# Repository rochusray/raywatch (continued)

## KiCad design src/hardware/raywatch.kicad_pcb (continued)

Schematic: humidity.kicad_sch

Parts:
C48: 100nF; C_0402_1005Metric
J57, J58: Conn_01x02_Pin; PinHeader_1x02_P1.27mm_Vertical
U18: ENS210-LQFM; XDCR_ENS210-LQFM; PARTREV 5

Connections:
+1V8: C48.1, J58.1, U18.1 (VDD); also elsewhere on the board
/Humidity/SCL1V8: J57.1, U18.2 (SCL)
/Humidity/SDA1V8: J57.2, U18.3 (SDA)
GND: C48.2, J58.2, U18.4 (VSS), U18.5 (VSS); also elsewhere on the board

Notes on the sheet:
I²C: 1000011

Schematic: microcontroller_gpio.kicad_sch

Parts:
J17, J21: Conn_02x08_Odd_Even; PinHeader_2x08_P1.27mm_Vertical
J18, J19, J20: Conn_01x02_Pin; PinHeader_1x02_P1.27mm_Vertical
R12, R13: 10kΩ; R_0402_1005Metric
U3, U4: PCAL6416AHF_128; QFN50P400X400X80-25N; PARTREV 7.1

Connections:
/GPIO/EXP1INT: J20.1, U4.22 (~INT)
/GPIO/EXP2INT: J20.2, U3.22 (~INT)
/GPIO/SCL: J19.1, U3.19 (SCL), U4.19 (SCL)
/GPIO/SDA: J19.2, U3.20 (SDA), U4.20 (SDA)
GND: J18.2, U3.9 (VSS), U3.25 (EXP), U4.9 (VSS), U4.18 (ADDR), U4.25 (EXP); also elsewhere on the board
unnamed: J17.1, U3.8 (P0_7)
unnamed: J17.2, U3.10 (P1_0)
unnamed: J17.3, U3.7 (P0_6)
unnamed: J17.4, U3.11 (P1_1)
unnamed: J17.5, U3.6 (P0_5)
unnamed: J17.6, U3.12 (P1_2)
unnamed: J17.7, U3.5 (P0_4)
unnamed: J17.8, U3.13 (P1_3)
unnamed: J17.9, U3.4 (P0_3)
unnamed: J17.10, U3.14 (P1_4)
unnamed: J17.11, U3.3 (P0_2)
unnamed: J17.12, U3.15 (P1_5)
unnamed: J17.13, U3.2 (P0_1)
unnamed: J17.14, U3.16 (P1_6)
unnamed: J17.15, U3.1 (P0_0)
unnamed: J17.16, U3.17 (P1_7)
unnamed: J21.1, U4.8 (P0_7)
unnamed: J21.2, U4.10 (P1_0)
unnamed: J21.3, U4.7 (P0_6)
unnamed: J21.4, U4.11 (P1_1)
unnamed: J21.5, U4.6 (P0_5)
unnamed: J21.6, U4.12 (P1_2)
unnamed: J21.7, U4.5 (P0_4)
unnamed: J21.8, U4.13 (P1_3)
unnamed: J21.9, U4.4 (P0_3)
unnamed: J21.10, U4.14 (P1_4)
unnamed: J21.11, U4.3 (P0_2)
unnamed: J21.12, U4.15 (P1_5)
unnamed: J21.13, U4.2 (P0_1)
unnamed: J21.14, U4.16 (P1_6)
unnamed: J21.15, U4.1 (P0_0)
unnamed: J21.16, U4.17 (P1_7)
unnamed: R12.2, U3.24 (~RESET)
unnamed: R13.2, U4.24 (~RESET)

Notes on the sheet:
I²C: 0100000

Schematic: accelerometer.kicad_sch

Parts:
C26, C27, C33, C34: 10µF; C_0402_1005Metric
C28, C29, C30, C31, C32, C35, C36, C37, C38: 100nF; C_0402_1005Metric
J37, J38, J39, J40, J41, J42, J43, J44, J45: Conn_01x02_Pin; PinHeader_1x02_P1.27mm_Vertical
U10, U11, U13, U14: LIS2DUX12TR; LGA-12_2.0X2.0X0.74_LIS2DUX12_STM
U12: TPS22916BYFPR; IC_TPS22916BYFPR; PARTREV F
Y3: DSC6003CE2A; OSC_DSC6003CE2A-000.0000; PARTREV B

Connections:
+1V8: C26.2, C27.2, C29.2, C31.2, C33.2, C34.2, C35.2, C37.2, J38.1, U10.9 (VDD), U11.9 (VDD), U13.9 (VDD), U14.9 (VDD); also elsewhere on the board
/Accelerometer/ACC1INT1: J41.1, U10.12 (INT1)
/Accelerometer/ACC1INT2: J41.2, U10.11 (INT2)
/Accelerometer/ACC2INT1: J43.1, U13.12 (INT1)
/Accelerometer/ACC2INT2: J43.2, U13.11 (INT2)
/Accelerometer/ACC3INT1: J42.1, U11.12 (INT1)
/Accelerometer/ACC3INT2: J42.2, U11.11 (INT2)
/Accelerometer/ACC4INT1: J44.1, U14.12 (INT1)
/Accelerometer/ACC4INT2: J44.2, U14.11 (INT2)
/Accelerometer/ACCCLK: U10.7 (RES), U11.7 (RES), U13.7 (RES), U14.7 (RES), Y3.3 (OUT)
/Accelerometer/ACCCLKEN: J45.1, U12.B2 (ON)
/Accelerometer/ACCCLKFS: J45.2, Y3.1 (OE)
/Accelerometer/SCL: J39.1, U11.1 (SCL/SPC), U14.1 (SCL/SPC)
/Accelerometer/SCL2: J40.1, U10.1 (SCL/SPC), U13.1 (SCL/SPC)
/Accelerometer/SDA: J39.2, U11.4 (SDA/SDI/SDO), U14.4 (SDA/SDI/SDO)
/Accelerometer/SDA2: J40.2, U10.4 (SDA/SDI/SDO), U13.4 (SDA/SDI/SDO)
GND: C26.1, C27.1, C28.2, C29.1, C30.2, C31.1, C32.2, C33.1, C34.1, C35.1, C36.2, C37.1, C38.2, J37.2, J38.2, U10.5 (NC), U10.6 (GND), U10.8 (GND), U11.5 (NC), U11.6 (GND), U11.8 (GND), U12.B1 (GND), U13.3 (SDO/SA0), U13.5 (NC), U13.6 (GND), U13.8 (GND), U14.3 (SDO/SA0), U14.5 (NC), U14.6 (GND), U14.8 (GND), Y3.2 (GND); also elsewhere on the board
unnamed: C28.1, U12.A1 (VOUT), Y3.4 (VDD)

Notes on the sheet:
I²C: 0011001
I²C: 0011000
Optional

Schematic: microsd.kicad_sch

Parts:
C39: 10µF; C_0402_1005Metric
C40: 100nF; C_0402_1005Metric
J46, J47: Conn_01x02_Pin; PinHeader_1x02_P1.27mm_Vertical
J48: Conn_01x04_Pin; PinHeader_1x04_P1.27mm_Vertical
J49: MSD-1-A; CUI_MSD-1-A; PARTREV 1.0
R19, R20, R25: 28Ω; R_0402_1005Metric
R21, R22, R23, R24, R26: 10kΩ; R_0402_1005Metric
U15: TPS22916BYFPR; IC_TPS22916BYFPR; PARTREV F

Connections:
/microSD/CS: J48.4, R25.1
/microSD/MISO: J48.3, J49.7 (DAT0), R21.2
/microSD/MOSI: J48.2, R20.1
/microSD/MSD3V3: C39.1, C40.1, J49.4 (VDD), R21.1, R22.1, R23.1, R24.1, U15.A1 (VOUT)
/microSD/MSDDET: J46.2, R26.1
/microSD/MSDEN: J46.1, U15.B2 (ON)
/microSD/SCK: J48.1, R19.1
GND: C39.2, C40.2, J47.2, J49.6 (VSS), J49.G1 (COVER_GND), J49.G2 (COVER_GND), J49.G3 (COVER_GND), J49.G4 (COVER_GND), U15.B1 (GND); also elsewhere on the board
unnamed: J49.2 (CD/DAT3), R24.2, R25.2
unnamed: J49.5 (CLK), R19.2
unnamed: J49.3 (CMD), R20.2
unnamed: J49.8 (DAT1), R22.2
unnamed: J49.1 (DAT2), R23.2
unnamed: J49.CD, R26.2

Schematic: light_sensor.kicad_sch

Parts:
C60: 1µF; C_0402_1005Metric; Tolerance 20%
J65, J66: Conn_01x02_Pin; PinHeader_1x02_P1.27mm_Vertical
U24: LTR-329ALS-01; IC_LTR-329ALS-01; PARTREV 1.8

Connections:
/Light Sensor/SCL: J66.1, U24.4 (SCL)
/Light Sensor/SDA: J66.2, U24.3 (SDA)
GND: C60.2, J65.2, U24.2 (GND); also elsewhere on the board

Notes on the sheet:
I²C: 0101001

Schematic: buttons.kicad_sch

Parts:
C18, C19, C20, C21: 10nF; C_0402_1005Metric
J22: Conn_01x02_Pin; PinHeader_1x02_P1.27mm_Vertical
J23: Conn_01x04_Pin; PinHeader_1x04_P1.27mm_Vertical
R14, R15, R16, R17: 200kΩ; R_0402_1005Metric
S1, S2, S3, S4: EVQ-P7A01P; SW_EVQ-P7A01P; PARTREV 2022.4

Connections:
/Buttons/BTN1: C18.1, J23.1, R14.2
/Buttons/BTN2: C19.1, J23.2, R15.2
/Buttons/BTN3: C20.1, J23.3, R16.2
/Buttons/BTN4: C21.1, J23.4, R17.2
GND: J22.2, S1.1_1, S1.1_2, S2.1_1, S2.1_2, S3.1_1, S3.1_2, S4.1_1, S4.1_2; also elsewhere on the board
unnamed: R14.1, S1.2_1, S1.2_2
unnamed: R15.1, S2.2_1, S2.2_2
unnamed: R16.1, S3.2_1, S3.2_2
unnamed: R17.1, S4.2_1, S4.2_2

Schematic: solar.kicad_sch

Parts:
B1, B2: KXOB25-05X3F-TR; CHIP2_KXOB25-05X3F-TR_AAR
C77, C78, C79: 10µF; C_0402_1005Metric
J86: Conn_01x02_Pin; PinHeader_1x02_P1.27mm_Vertical
L9: 2.2µH; L_0402_1005Metric
R39: 400KΩ; R_0402_1005Metric
R40: 100KΩ; R_0402_1005Metric
U33: TPS61099YFFT; YFF0006AFAD

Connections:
GND: B1.1, B2.1, C77.2, C78.2, C79.2, J86.2, R40.2, U33.A2 (GND); also elsewhere on the board
unnamed: B1.2, B2.2, C77.1, L9.1, U33.A1 (VIN), U33.C1 (EN)
unnamed: R39.2, R40.1, U33.C2 (FB)
unnamed: L9.2, U33.B1 (SW)
VSOLAR: C78.1, C79.1, J86.1, R39.1, U33.B2 (VOUT); also elsewhere on the board

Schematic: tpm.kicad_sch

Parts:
C25: 100nF; C_0402_1005Metric
J35, J36: Conn_01x02_Pin; PinHeader_1x02_P1.27mm_Vertical
U9: ATECC608A-MAHDA-S; SON50P200X300X60-9N

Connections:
/TPM/SCL: J36.1, U9.6 (SCL)
/TPM/SDA: J36.2, U9.5 (SDA)
GND: C25.2, J35.2, U9.4 (GND), U9.9 (GND_PAD); also elsewhere on the board

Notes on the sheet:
Default I²C: 1100000

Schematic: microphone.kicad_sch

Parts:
C96: 100nF; C_0402_1005Metric
J90, J91: Conn_01x02_Pin; PinHeader_1x02_P1.27mm_Vertical
U36: IM72D128V01XTMA1; PG-LLGA-5-3_INF

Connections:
/Microphone/PDMCLK: J91.2, U36.3 (CLOCK)
/Microphone/PDMDATA: J91.1, U36.1 (DATA)
GND: C96.2, J90.2, U36.4 (SELECT), U36.5 (GND); also elsewhere on the board

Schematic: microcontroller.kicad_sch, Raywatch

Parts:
ANT1: SR4W035; SR4W035_4X6_ANT
ANT2: W3102; IND_W3102; PARTREV 1944
C1: 1.5pF; C_0402_1005Metric; Rated Voltage 25V; Tolerance 0.05pF
C2: 2pF; C_0402_1005Metric; Rated Voltage 25V; Tolerance 0.05pF
C3: 3.9pF; C_0402_1005Metric
C4: 3pF; C_0402_1005Metric; Rated Voltage 50V; Tolerance 0.1pF
C5: 1.5pF; C_0402_1005Metric; Rated Voltage 50V; Tolerance 20%
C6, C11, C13, C15: 100nF; C_0402_1005Metric; Rated Voltage 3.3V; Tolerance 10%
C7, C8: 27pF; C_0402_1005Metric; Tolerance 2%
C9: 10µF; C_0402_1005Metric; Rated Voltage 6.3V; Tolerance 20%
C10, C17: 2.2µF; C_0402_1005Metric; Rated Voltage 3.3V; Tolerance 20%
C12: 2.2nF; C_0402_1005Metric; Rated Voltage 10V; Tolerance 10%
C14: 10nF; C_0402_1005Metric; Rated Voltage 6.3V
C16: 100pF; C_0402_1005Metric
FB1: 120Ω; L_0402_1005Metric
J1: Conn_02x05_Odd_Even; PinHeader_2x05_P1.27mm_Vertical
J2, J3, J4, J5, J12, J13: Conn_01x02_Pin; PinHeader_1x02_P1.27mm_Vertical
J6, J7, J8, J9, J10, J11: Conn_01x04_Pin; PinHeader_1x04_P1.27mm_Vertical
J14, J15, J16: Conn_02x08_Odd_Even; PinHeader_2x08_P1.27mm_Vertical
L1: 2.7nH; L_0402_1005Metric
L2, L3: 2.5nH; L_0402_1005Metric
L4: -; L_0402_1005Metric; not fitted
L5: 2.2nH; L_0402_1005Metric
L6: 4.7µH; L_0402_1005Metric; Tolerance 20%
R1, R2, R3: 1kΩ; R_0402_1005Metric
R4: 200kΩ; R_0402_1005Metric
R5: 100kΩ; R_0402_1005Metric
R6, R7, R8, R9, R10, R11: 10kΩ; R_0402_1005Metric
U1: NRF54L15-QFAA-R; QFN40P600X600X90-49N; PARTREV 0.8
U2: PCA9306DQER; SON35P140X100X40-8N
Y1: ABS07-32.768KHZ-7-T; XTAL_ABS07-32.768KHZ-7-T; PARTREV 08.19.15
Y2: ECS-320-8-37B-CKY-TR; XTAL_ECS-160-9-37-CKM-TR; PARTREV 2017

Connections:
+1V8: J3.1, U2.2 (VREF1); also elsewhere on the board
/MC: Microcontroller/ANT: J13.1, L1.2, U1.31 (ANT)
/MC: Microcontroller/NFC1: ANT2.1, C7.2, J2.1, U1.3 (P1.02/NFC1)
/MC: Microcontroller/NFC2: ANT2.2, C8.1, J2.2, U1.4 (P1.03/NFC2)
/MC: Microcontroller/P2.07: J1.6, J10.2, U1.18 (P2.07/TRACEDATA(0)/SWO)
/MC: Microcontroller/PDMCLK: J12.2, U1.42 (P1.14/RADIO(5)/AIN7)
/MC: Microcontroller/PDMDATA: J12.1, R5.1, U1.41 (P1.13/RADIO(4)/AIN6)
/MC: Microcontroller/SCL: J15.2, J15.4, J15.6, J15.8, J15.10, J15.12, J15.14, J15.16, R7.1, U1.28 (P0.03/GRTCPWM), U2.6 (SCL2)
/MC: Microcontroller/SCL1V8: J16.2, J16.4, J16.6, J16.8, J16.10, J16.12, J16.14, J16.16, R9.1, U2.3 (SCL1)
/MC: Microcontroller/SCL2: J14.2, J14.4, J14.6, J14.8, J14.10, J14.12, J14.14, J14.16, R11.1, U1.9 (P1.08/CLK16M/EXTREF)
/MC: Microcontroller/SDA: J15.1, J15.3, J15.5, J15.7, J15.9, J15.11, J15.13, J15.15, R6.1, U1.27 (P0.02), U2.5 (SDA2)
/MC: Microcontroller/SDA1V8: J16.1, J16.3, J16.5, J16.7, J16.9, J16.11, J16.13, J16.15, R8.1, U2.4 (SDA1)
/MC: Microcontroller/SDA2: J14.1, J14.3, J14.5, J14.7, J14.9, J14.11, J14.13, J14.15, R10.1, U1.8 (P1.07/ASI(1)/AIN3)
/MC: Microcontroller/VSSPA: C1.2, J13.2, U1.32 (VSS_PA)
/MC: Microcontroller/XC1: U1.34 (XC1), Y2.1 (IN/OUT)
/MC: Microcontroller/XC2: U1.35 (XC2), Y2.3 (OUT/IN)
GND: ANT1.3 (GND), ANT1.4 (GND), ANT1.6 (GND), C2.2, C3.1, C4.2, C6.2, C7.1, C8.2, C9.2, C10.2, C11.1, C12.2, C13.1, C14.2, C15.2, C16.2, C17.2, J1.3, J1.5, J1.9, J3.2, J4.2, J6.4, J7.4, J11.4, L4.2, L5.2, R5.2, R6.2, R7.2, R8.2, R9.2, R10.2, R11.2, U1.44 (VSS), U1.49 (VSS), U2.1 (GND), Y2.2 (GND), Y2.4 (GND); also elsewhere on the board
unnamed: ANT1.2 (FEED), C5.2, L5.1
unnamed: C1.1, L1.1, L2.2
unnamed: C2.1, L2.1, L3.2
unnamed: C4.1, C5.1, L3.1, L4.1
unnamed: J1.2, U1.25 (SWDIO)
unnamed: J1.4, U1.26 (SWDCLK)
unnamed: J1.10, R1.1
unnamed: J5.1, R2.1
unnamed: J5.2, R3.1
unnamed: J6.1, U1.5 (P1.04/ASO(0)/AIN0)
unnamed: J6.2, U1.6 (P1.05/ASI(0)/RADIO(6)/AIN1)
unnamed: J6.3, U1.7 (P1.06/ASO(1)/AIN2)
unnamed: J7.1, U1.23 (P0.00)
unnamed: J7.2, U1.24 (P0.01)
unnamed: J7.3, U1.29 (P0.04/GRTCLFCLKOUT)
unnamed: J8.1, U1.37 (P1.09/ASO(2)/RADIO(0))
unnamed: J8.2, U1.38 (P1.10/ASI(2)/RADIO(1))
unnamed: J8.3, U1.39 (P1.11/ASO(3)/RADIO(2)/AIN4)
unnamed: J8.4, U1.40 (P1.12/ASI(3)/RADIO(3)/AIN5)
unnamed: J9.1, U1.11 (P2.00)
unnamed: J9.2, U1.12 (P2.01)
unnamed: J9.3, U1.13 (P2.02)
unnamed: J9.4, U1.14 (P2.03)
unnamed: J10.1, U1.17 (P2.06/TRACECLK)
unnamed: J10.3, U1.19 (P2.08/TRACEDATA(1))
unnamed: J10.4, U1.20 (P2.09/TRACEDATA(2))
unnamed: J11.1, U1.15 (P2.04)
unnamed: J11.2, U1.16 (P2.05)
unnamed: J11.3, U1.21 (P2.10/TRACEDATA(3))
unnamed: L6.2, U1.46 (DCC)
unnamed: C12.1, C14.1, C17.1, FB1.1, U1.33 (DECRF), U1.43 (DECA)
unnamed: C10.1, FB1.2, L6.1, U1.45 (DECD)
unnamed: U1.1 (P1.00/XL1), Y1.2
unnamed: U1.2 (P1.01/XL2), Y1.1
unnamed: C3.2, R1.2, R2.2, R3.2, U1.30 (~RESET)
unnamed: C16.1, R4.1, U2.7 (VREF2), U2.8 (EN)

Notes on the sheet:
Matching using reference board circuit
Matching just eyeballed

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
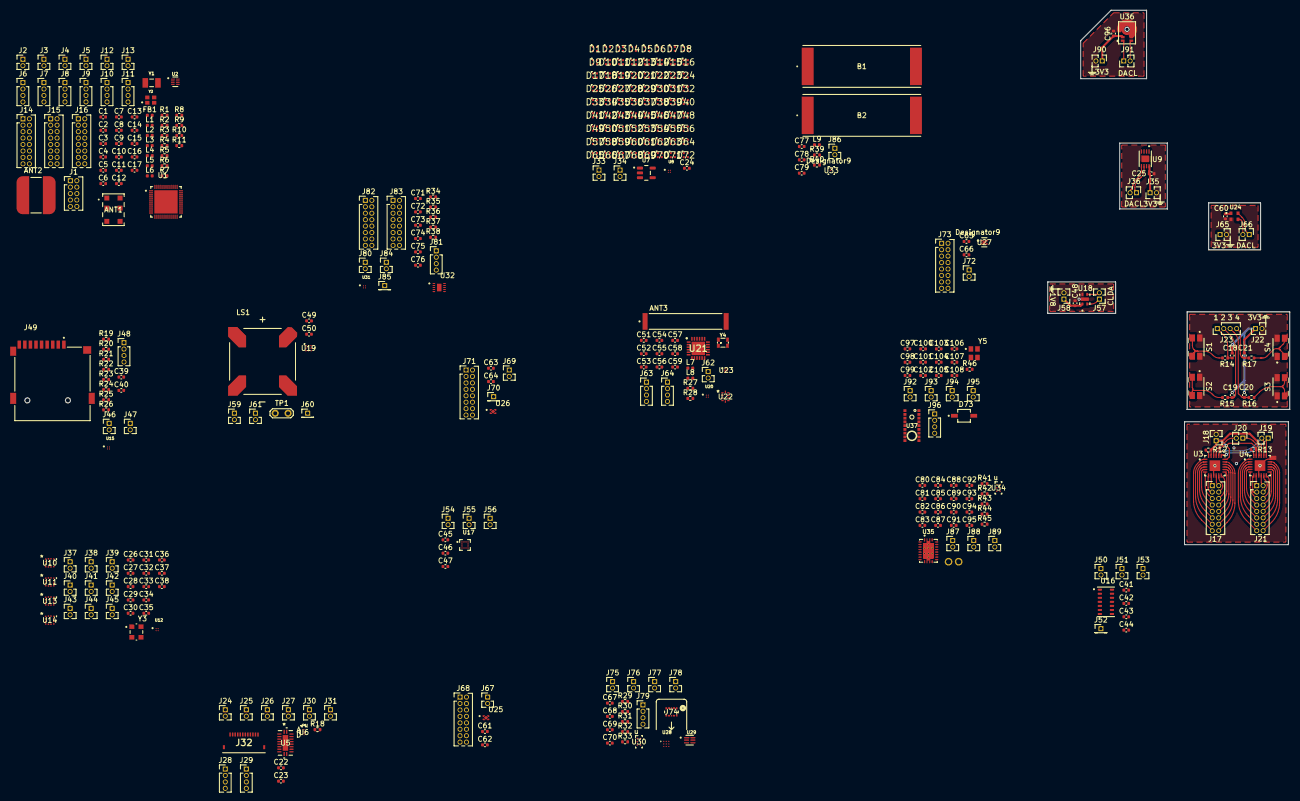
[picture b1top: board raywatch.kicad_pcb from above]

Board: 2 copper layers, 387 parts (0 on the bottom side), 322 nets.
